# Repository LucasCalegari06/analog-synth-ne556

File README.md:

# 1-Octave Analog Synthesizer (NE556 / NE555)

An autonomous analog audio synthesizer designed to reproduce the fundamental frequencies of a full musical octave. Built using NE556 dual timer ICs and an NE555 timer, this project features integrated analog signal conditioning, hardware circuit protection, and a compact custom 2-layer PCB designed in KiCad.

## Project Overview & Engineering Highlights

- **Multi-Oscillator Tone Generation:** Designed dedicated astable multivibrator stages for each musical note in an octave using multiple NE556 timer ICs (and an NE555), allowing polyphonic and independent frequency tuning.
- **Signal Conditioning & AC Coupling:** 
  - Standard 555 output stages produce high-amplitude unipolar square waves (0 to V<sub>CC</sub>).
  - Integrated series AC coupling capacitors to eliminate DC bias.
  - Implemented resistive attenuation dividers to scale the output down to standard line-level audio.
- **Hardware Clamping & Overvoltage Protection:** Added antiparallel diode limiters across the output path to shunt transient voltage spikes directly to ground, protecting connected external audio interfaces / PC sound cards.
- **Tolerance Calibration:** Compensated for real-world passive component tolerances (*Bauteiltoleranzen*) by pairing fixed precision resistors with manual trimming potentiometers for calibration.
- **PCB Layout & Constraints:**
  - Designed within standard $100 \times 100\text{ mm}$ manufacturing boundaries.
  - Employed predominantly SMD passive components to achieve high component density and clean trace routing.
  - Routed dedicated headers for external key contacts and multi-purpose audio output jacks (line-out / speaker).

## Hardware Specifications

| Parameter | Specification |
| :--- | :--- |
| **Oscillators** | NE556 Dual Timers + NE555 (Astable Configuration) |
| **Target Bandwidth** | 1 Musical Octave (Equal Temperament frequencies) |
| **Output Protection** | Antiparallel Diode Clipping to GND + Series AC Blocking |
| **PCB Dimensions** | $100 \text{ mm} \times 100 \text{ mm}$ (2-layer FR4) |
| **Component Package** | Mixed SMD (passives/ICs) & THT (headers/trimming pots) |
| **EDA Tool** | KiCad 10.0 |

## Circuit & Layout Gallery

<table>
  <tr>
    <td align="center" width="50%">
      
      <br />
      <b>Schematic Overview (<a href="hardware/outputs/schematic.pdf">Download PDF</a>)</b>
    </td>
    <td align="center" width="50%">
      
      <br />
      <b>2-Layer PCB Trace Layout</b>
    </td>
  </tr>
</table>

## Simulation & Verification

The oscillator stages, passive AC coupling, and diode clamping network were verified through circuit simulation prior to schematic capture and layout.

- **Interactive Simulation:** [Run 1-Octave Synthesizer in Falstad](https://www.falstad.com/s.py?s=KYIuwd)
- **Circuit Data:** Raw netlist available at [`simulation/falstad_circuit.txt`](simulation/falstad_circuit.txt)

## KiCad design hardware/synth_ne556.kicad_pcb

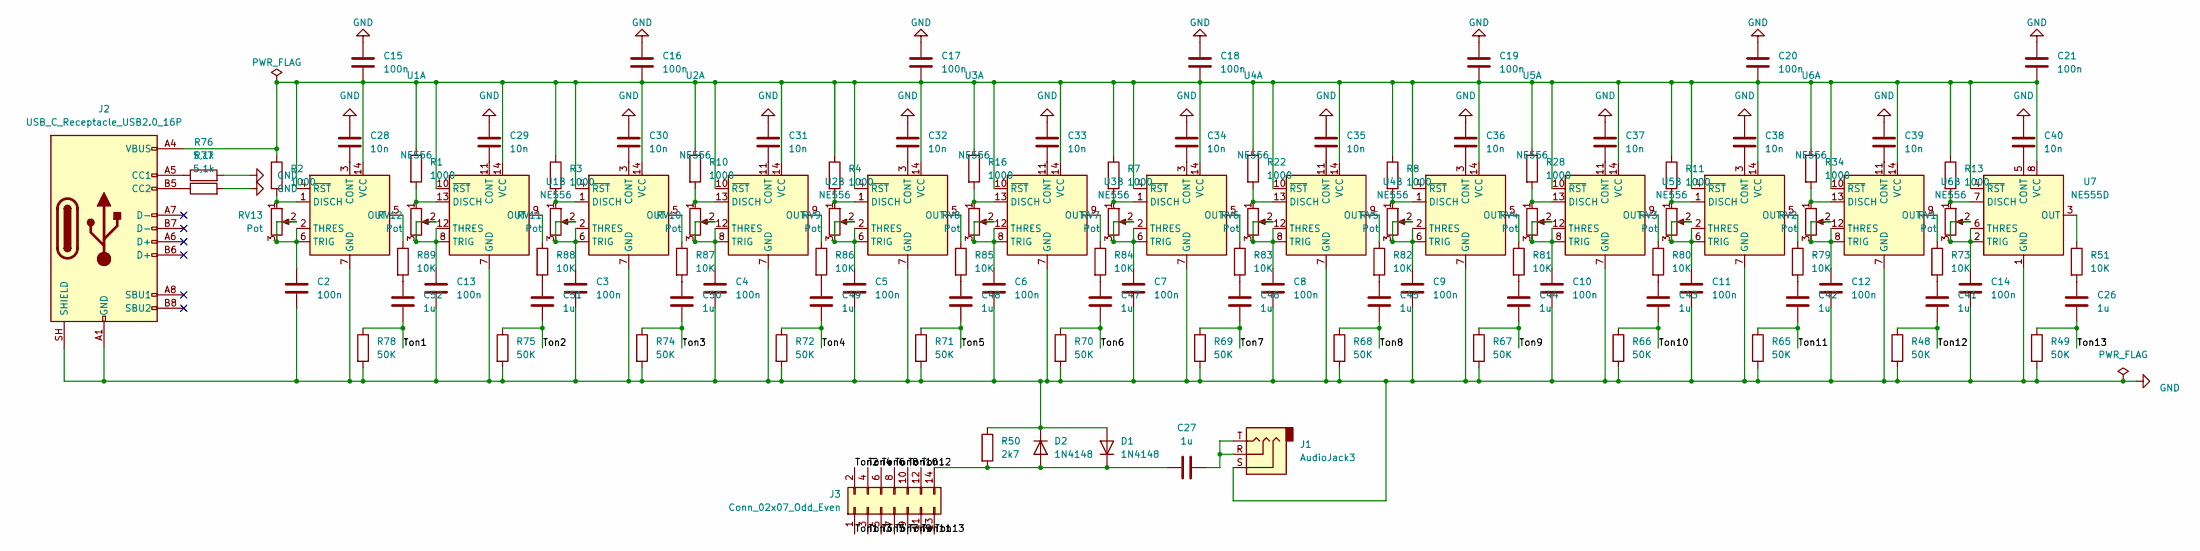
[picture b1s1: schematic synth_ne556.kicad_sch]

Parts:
C2, C3, C4, C5, C6, C7, C8, C9, C10, C11, C12, C13, C14, C15, C16, C17, C18, C19, C20, C21: 100n; C_0805_2012Metric_Pad1.18x1.45mm_HandSolder
C26, C27, C41, C42, C43, C44, C45, C46, C47, C48, C49, C50, C51, C52: 1u; C_0805_2012Metric_Pad1.18x1.45mm_HandSolder
C28, C29, C30, C31, C32, C33, C34, C35, C36, C37, C38, C39, C40: 10n; C_0805_2012Metric_Pad1.18x1.45mm_HandSolder
D1, D2: 1N4148; D_DO-35_SOD27_P7.62mm_Horizontal
J1: AudioJack3; Jack_3.5mm_PJ320D_Horizontal
J2: USB_C_Receptacle_USB2.0_16P; USB_C_Receptacle_HRO_TYPE-C-31-M-12
J3: Conn_02x07_Odd_Even; IDC-Header_2x07_P2.54mm_Vertical
R1, R2, R3, R4, R7, R8, R10, R11, R13, R16, R22, R28, R34: 1000; R_0805_2012Metric_Pad1.20x1.40mm_HandSolder
R48, R49, R65, R66, R67, R68, R69, R70, R71, R72, R74, R75, R78: 50K; R_0805_2012Metric_Pad1.20x1.40mm_HandSolder
R50: 2k7; R_0805_2012Metric_Pad1.20x1.40mm_HandSolder
R51, R73, R79, R80, R81, R82, R83, R84, R85, R86, R87, R88, R89: 10K; R_0805_2012Metric_Pad1.20x1.40mm_HandSolder
R76, R77: 5,1k; R_0805_2012Metric_Pad1.20x1.40mm_HandSolder
RV1, RV2, RV3, RV4, RV5, RV6, RV7, RV8, RV9, RV10, RV11, RV12, RV13: Pot; Potentiometer_Bourns_3296W_Vertical
U1, U2, U3, U4, U5, U6: NE556; SOIC-14_3.9x8.7mm_P1.27mm
U7: NE555D; SOIC-8_3.9x4.9mm_P1.27mm

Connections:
/Ton1: C52.2, J3.1, R78.1
/Ton2: C51.2, J3.2, R75.1
/Ton3: C50.2, J3.3, R74.1
/Ton4: C49.2, J3.4, R72.1
/Ton5: C48.2, J3.5, R71.1
/Ton6: C47.2, J3.6, R70.1
/Ton7: C46.2, J3.7, R69.1
/Ton8: C45.2, J3.8, R68.1
/Ton9: C44.2, J3.9, R67.1
/Ton10: C43.2, J3.10, R66.1
/Ton11: C42.2, J3.11, R65.1
/Ton12: C41.2, J3.12, R48.1
/Ton13: C26.2, J3.13, R49.1
GND: C2.2, C3.2, C4.2, C5.2, C6.2, C7.2, C8.2, C9.2, C10.2, C11.2, C12.2, C13.2, C14.2, C15.2, C16.2, C17.2, C18.2, C19.2, C20.2, C21.2, C28.1, C29.1, C30.1, C31.1, C32.1, C33.1, C34.1, C35.1, C36.1, C37.1, C38.1, C39.1, C40.1, D1.2 (A), D2.1 (K), J1.S, J2.A1 (GND), J2.A12 (GND), J2.B1 (GND), J2.B12 (GND), J2.SH (SHIELD), R48.2, R49.2, R50.1, R65.2, R66.2, R67.2, R68.2, R69.2, R70.2, R71.2, R72.2, R74.2, R75.2, R76.2, R77.2, R78.2, U1.7 (GND), U2.7 (GND), U3.7 (GND), U4.7 (GND), U5.7 (GND), U6.7 (GND), U7.1 (GND)
unnamed: C26.1, R51.2
unnamed: C27.2, J1.R, J1.T
unnamed: C41.1, R73.2
unnamed: C42.1, R79.2
unnamed: C43.1, R80.2
unnamed: C44.1, R81.2
unnamed: C45.1, R82.2
unnamed: C46.1, R83.2
unnamed: C47.1, R84.2
unnamed: C48.1, R85.2
unnamed: C49.1, R86.2
unnamed: C50.1, R87.2
unnamed: C51.1, R88.2
unnamed: C52.1, R89.2
unnamed: C27.1, D1.1 (K), D2.2 (A), J3.14, R50.2
unnamed: J2.A5 (CC1), R76.1
unnamed: J2.B5 (CC2), R77.1
unnamed: C28.2, U1.3 (CONT)
unnamed: R2.2, RV13.1, U1.1 (DISCH)
unnamed: R89.1, U1.5 (OUT)
unnamed: C2.1, RV13.2, RV13.3, U1.2 (THRES), U1.6 (TRIG)
unnamed: C15.1, C16.1, C17.1, C18.1, C19.1, C20.1, C21.1, J2.A4 (VBUS), J2.A9 (VBUS), J2.B4 (VBUS), J2.B9 (VBUS), R1.1, R2.1, R3.1, R4.1, R7.1, R8.1, R10.1, R11.1, R13.1, R16.1, R22.1, R28.1, R34.1, U1.4 (~RST), U1.10 (~RST), U1.14 (VCC), U2.4 (~RST), U2.10 (~RST), U2.14 (VCC), U3.4 (~RST), U3.10 (~RST), U3.14 (VCC), U4.4 (~RST), U4.10 (~RST), U4.14 (VCC), U5.4 (~RST), U5.10 (~RST), U5.14 (VCC), U6.4 (~RST), U6.10 (~RST), U6.14 (VCC), U7.4 (~RST), U7.8 (VCC)
unnamed: C29.2, U1.11 (CONT)
unnamed: R1.2, RV12.1, U1.13 (DISCH)
unnamed: R88.1, U1.9 (OUT)
unnamed: C13.1, RV12.2, RV12.3, U1.8 (TRIG), U1.12 (THRES)
unnamed: C30.2, U2.3 (CONT)
unnamed: R3.2, RV11.1, U2.1 (DISCH)
unnamed: R87.1, U2.5 (OUT)
unnamed: C3.1, RV11.2, RV11.3, U2.2 (THRES), U2.6 (TRIG)
unnamed: C31.2, U2.11 (CONT)
unnamed: R10.2, RV10.1, U2.13 (DISCH)
unnamed: R86.1, U2.9 (OUT)
unnamed: C4.1, RV10.2, RV10.3, U2.8 (TRIG), U2.12 (THRES)
unnamed: C32.2, U3.3 (CONT)
unnamed: R4.2, RV9.1, U3.1 (DISCH)
unnamed: R85.1, U3.5 (OUT)
unnamed: C5.1, RV9.2, RV9.3, U3.2 (THRES), U3.6 (TRIG)
unnamed: C33.2, U3.11 (CONT)
unnamed: R16.2, RV8.1, U3.13 (DISCH)
unnamed: R84.1, U3.9 (OUT)
unnamed: C6.1, RV8.2, RV8.3, U3.8 (TRIG), U3.12 (THRES)
unnamed: C34.2, U4.3 (CONT)
unnamed: R7.2, RV7.1, U4.1 (DISCH)
unnamed: R83.1, U4.5 (OUT)
unnamed: C7.1, RV7.2, RV7.3, U4.2 (THRES), U4.6 (TRIG)
unnamed: C35.2, U4.11 (CONT)
unnamed: R22.2, RV6.1, U4.13 (DISCH)
unnamed: R82.1, U4.9 (OUT)
unnamed: C8.1, RV6.2, RV6.3, U4.8 (TRIG), U4.12 (THRES)
unnamed: C36.2, U5.3 (CONT)
unnamed: R8.2, RV5.1, U5.1 (DISCH)
unnamed: R81.1, U5.5 (OUT)
unnamed: C9.1, RV5.2, RV5.3, U5.2 (THRES), U5.6 (TRIG)
unnamed: C37.2, U5.11 (CONT)
unnamed: R28.2, RV4.1, U5.13 (DISCH)
unnamed: R80.1, U5.9 (OUT)
unnamed: C10.1, RV4.2, RV4.3, U5.8 (TRIG), U5.12 (THRES)
unnamed: C38.2, U6.3 (CONT)
unnamed: R11.2, RV3.1, U6.1 (DISCH)
unnamed: R79.1, U6.5 (OUT)
unnamed: C11.1, RV3.2, RV3.3, U6.2 (THRES), U6.6 (TRIG)
unnamed: C39.2, U6.11 (CONT)
unnamed: R34.2, RV2.1, U6.13 (DISCH)
unnamed: R73.1, U6.9 (OUT)
unnamed: C12.1, RV2.2, RV2.3, U6.8 (TRIG), U6.12 (THRES)
unnamed: C40.2, U7.5 (CONT)
unnamed: R13.2, RV1.1, U7.7 (DISCH)
unnamed: R51.1, U7.3 (OUT)
unnamed: C14.1, RV1.2, RV1.3, U7.2 (TRIG), U7.6 (THRES)

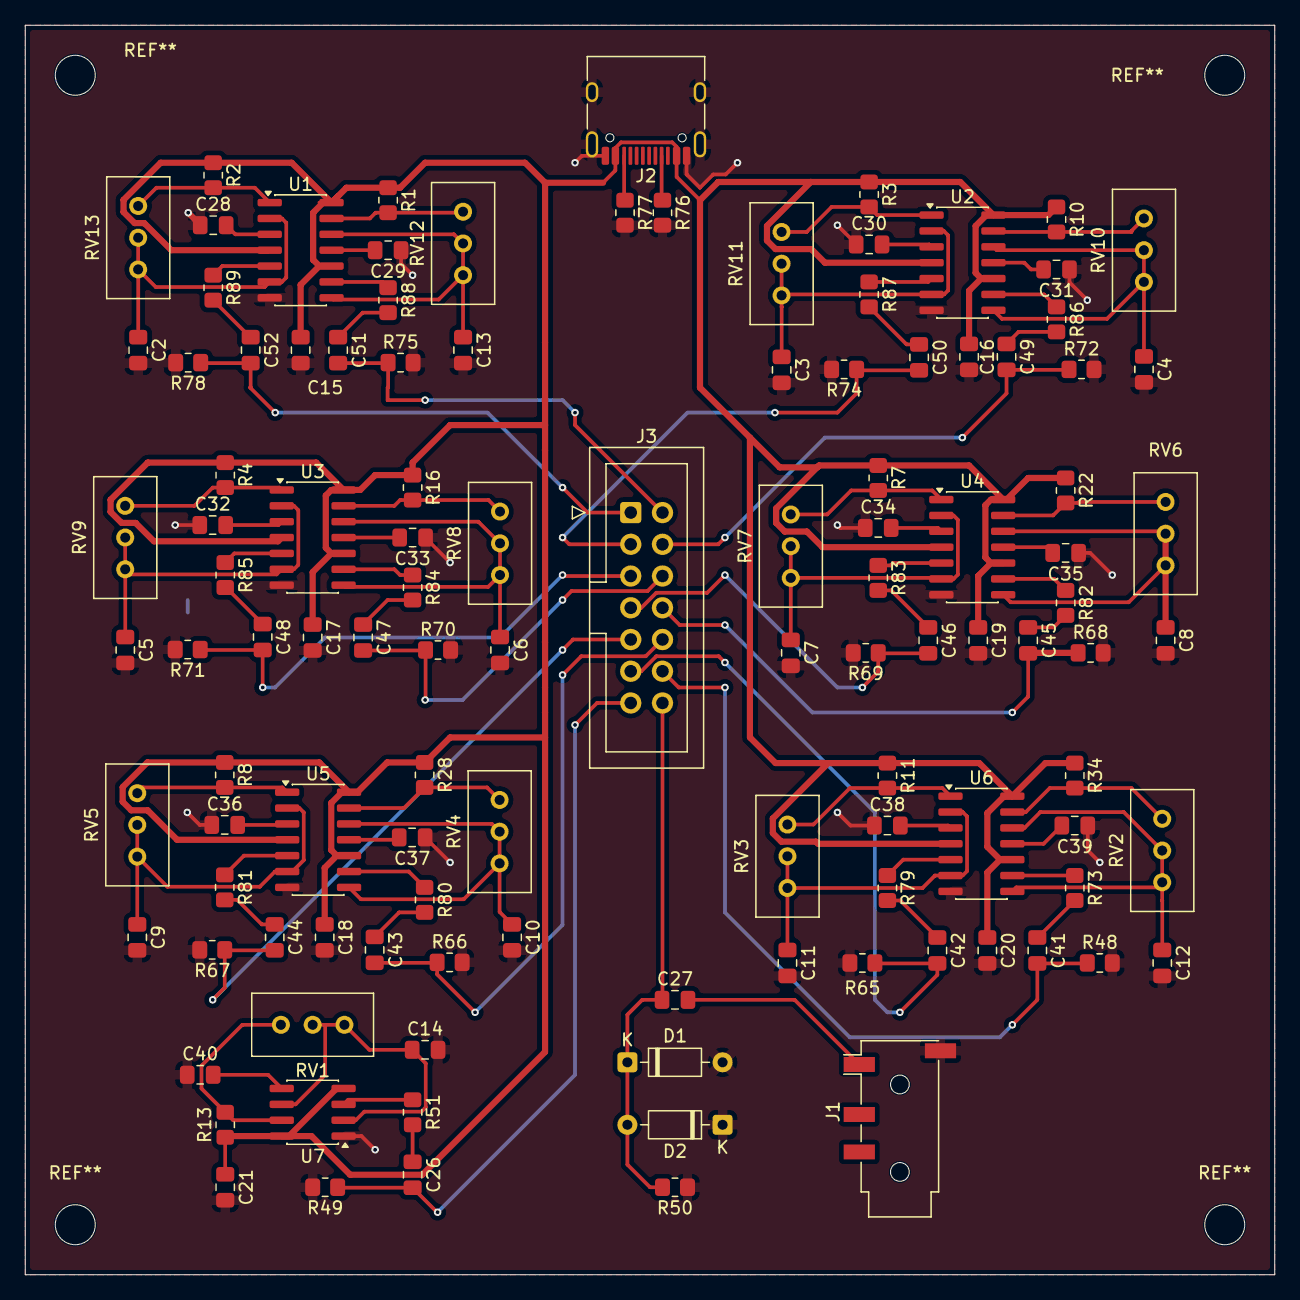
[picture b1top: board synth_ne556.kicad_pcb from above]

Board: 2 copper layers, 100.0 x 100.0 mm, 114 parts (0 on the bottom side), 84 nets.
